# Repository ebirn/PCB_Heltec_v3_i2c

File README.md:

poka-yoke from: https://github.com/PabloOyarzo/poka-yoke_rxtx/tree/main

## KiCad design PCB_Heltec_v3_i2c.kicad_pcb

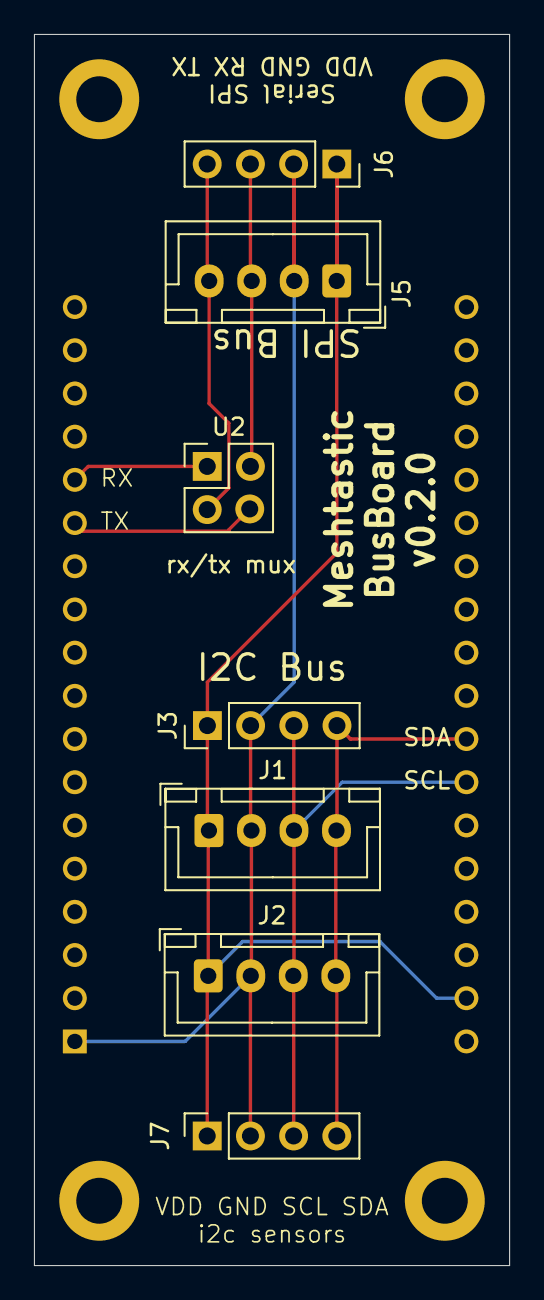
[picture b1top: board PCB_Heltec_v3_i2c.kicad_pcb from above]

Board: 2 copper layers, 27.9 x 72.4 mm, 8 parts (1 on the bottom side), 7 nets.

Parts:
J1, J2: i2c; JST_XH_B4B-XH-A_1x04_P2.50mm_Vertical
J3: i2c; PinHeader_1x04_P2.54mm_Vertical
J5: Conn_01x04_Pin; JST_XH_B4B-XH-A_1x04_P2.50mm_Vertical
J6, J7: PINHD_1x4_Female; PinSocket_1x04_P2.54mm_Vertical
U1: ESP32_LORA_V2.0; MODULE_ESP32_LORA_V2.0
U2: PinHeader_2x02_P2.54mm_Vertical

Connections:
/SCL: J1.3, J2.3, J3.3, J7.3, U1.J3_7 (ADC1_3/GPI39/39)
/SDA: J1.4, J2.4, J3.4, J7.4, U1.J3_8 (LORA_DIO2/ADC1_6/GPI34/34)
GND: J1.2, J2.2, J3.2, J5.2, J6.2, J7.2, U1.J2_1 (GND), U1.J3_1 (GND)
unnamed: U1.J2_3 (VEXT), U1.J2_4 (VEXT)
RX: J5.4, J6.4, U1.J2_14 (OLED_SCL/TOUCH3/HSPI_CSO/ADC2_3/GPIO15/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), U2.1 (Rx_In), U2.4 (Rx_Out)
TX: J5.3, J6.3, U1.J2_13 (LORA_SCK/V_SPI_CS0/GPIO5/5), U2.2 (Tx_In), U2.3 (Tx_Out)
VDD: J1.1, J2.1, J3.1, J5.1, J6.1, J7.1, U1.J3_2 (3V3), U1.J3_3 (3V3)

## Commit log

2025-02-16 initial version for HeltecV3 i2c and (uart?, for gps) breakout board
2025-03-16 fix CDD net routing, replace rx/tx mux with pin header instead smd pads, reduce board width
